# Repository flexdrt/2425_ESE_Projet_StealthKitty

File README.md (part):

# 🐱 **StealthKitty - Projet Robot Chat**  

---

## 📜 **Description**  
StealthKitty est un projet de **système embarqué innovant** basé sur un **STM32**.  
🎯 **Objectif :** Développer plusieurs robots capables de se déplacer sur une table sans bordure.  

- 🐾 Un robot est désigné comme chat et doit attraper un autre robot, qui devient alors le nouveau chat.  

Ce projet est réalisé dans le cadre de la dernière année de la filière **électronique et systèmes embarqués (ESE)** de l'ENSEA.

### **Les contributeurs :**  
- 👨‍💻 **Vincent LAKHMECHE**  
- 👨‍💻 **Mohamed Rafik CHAIR**  
- 👨‍💻 **Meziane Ameur**  
- 👨‍💻 **Karim JERJOUB**

---

## 📚 **Table des matières**
1. [📖 Contexte](#-contexte)
2. [📐 Architecture](#-architecture)  
3. [✨ Fonctionnalités](#-fonctionnalités)
4. [📚 Explication Technique](#-Explication-Technique). 
5. [🔧 Matériel utilisé](#-matériel-utilisé)  
6. [🚀 Utilisation](#-utilisation)  
7. [📄 Licence](#-licence)  

---

## 📖 **Contexte**  
Ce projet s'inscrit dans le cadre de la formation 3A à l'ENSEA.  
🎯 L'objectif est de concevoir un système embarqué complet, depuis la conception électronique jusqu'à l'implémentation logicielle.

---

## 📐 **Architecture**  
### **Schéma architectural**  

Ce schéma ne détaille pas que chaque moteur a sa propre pwm et son driver propre également.

## Explication du fonctionnement du système

1. **⚡ Alimentation principale**
   - La **batterie NiMH 7.2V 1.3Ah** alimente l'ensemble du système. Elle est connectée à des régulateurs de tension pour fournir les différentes tensions nécessaires aux composants :
     - **MP1475S** : Régulateur 5V pour alimenter les moteurs et certains capteurs.
     - **BU33SD5WG-TR** : Régulateur 3.3V pour alimenter le microcontrôleur STM32G431, l'accéléromètre et le LiDAR.

2. **🖥️ Microcontrôleur principal - STM32G431**
   - Le **STM32G431** gère toute la logique du robot et communique avec les différents composants via des bus tels que SPI, UART, I2C.
   - Il est relié à un **quartz 16 MHz** pour la gestion de l'horloge système et dispose d'un connecteur **SWD** pour la programmation et le débogage.

3. **🔍 Capteurs**
   - **Capteurs ToF** : Utilisés pour détecter les bords ou les chutes du robot.
   - **ADXL343 (Accéléromètre)** : Détecte les impacts ou les tapotements, utilisé pour détecter les collisions avec d'autres robots, et connecté au bus **SPI**.
   - **LiDAR YDLIDAR X4** : Permet de détecter les obstacles à l'aide de la communication **UART** pour transmettre les données de distance et d'angle.

4. **⚙️ Contrôle des moteurs**
   - **ZXBM5210-SP-13 (Driver de moteur)** : Utilisé pour contrôler la direction et la vitesse des moteurs à l'aide de signaux **PWM**. Le microcontrôleur STM32 contrôle les moteurs via le driver pour ajuster la vitesse et la direction du robot.

5. **🌟 Indicateurs d'état (LEDs)**
   - Les **LEDs** servent d'indicateurs pour visualiser l'état du robot, par exemple, lorsqu'il est en marche ou lorsqu'il détecte un obstacle.

### Détails des principaux outils utilisés

1. **Communication avec l'accéléromètre (ADXL343)**
   - Utilisation du protocole **SPI** pour lire les données des axes X, Y et Z.
   - Détection des chocs (taps) causés par des collisions avec d'autres robots.

2. **Contrôle des moteurs avec le driver ZXBM5210**
   - Génération de signaux **PWM** pour réguler la vitesse des moteurs.
   - Implémentation des mouvements du robot : avancer, reculer, tourner à gauche ou à droite.

3. **Gestion des capteurs de bordure/détection de chute**
   - Lecture des entrées des capteurs pour détecter les bords de la table.
   - Réaction immédiate pour stopper ou changer de direction afin d’éviter une chute.

4. **Interfaçage avec le LiDAR YDLIDAR X4**
   - Communication via **UART** pour lire les données du LiDAR ainsi détecter les autres robots.
   - Extraction des valeurs d’angles et de distances pour cartographier l'environnement et éviter les obstacles.

---

## ✨ **Fonctionnalités**  
- 🛡️ **Détection de bords** via des capteurs ToF.  
- 🔄 **Communication entre robots** pour synchronisation.  
- 🎯 **Algorithme de poursuite et d'évitement.**  
- ⚙️ **Gestion des moteurs**
  
## 📚 Explication Technique

#  ⚡Accéléromètre ADXL343 dans le robot chat

<details>
<summary> Détail  sur l'utilisation de l'accéléromètre ADXL343 </summary>

## 🎯 Objectifs principaux
- ✨ **Détecter les tapotements** (Single Tap/Double Tap) pour **changer de rôle** entre le robot dans l'état "chat" et dans l'état "souris".
- 📊 Lire les valeurs d'accélération sur les axes **X, Y, Z** *(optionnel)*.

---

## ⚙️ Configuration
- **Plage d'accélération :** ±2 g *(précision pour petits mouvements)*.
- **Registres utilisés :**  
  - 🛠️ `POWER_CTL` : Activer le mode mesure.  
  - 🎚️ `THRESH_TAP`, `DUR`, `INT_ENABLE` : Configurer les seuils et activer les interruptions pour les tapotements.  
  - 🖥️ `INT_SOURCE` : Vérifier les événements de tapotements.

---

## 🔧 Fonctionnalités implémentées
### ✅ Détection des tapotements
- 🔄 Vérifie les interruptions via le registre `INT_SOURCE`.
- 📍 Met à jour la variable globale `tap_detected` pour signaler un événement.

### ✅ Lecture des accélérations
- 📥 Récupération des valeurs brutes : `acc_rawX`, `acc_rawY`, `acc_rawZ`.
- 🔄 Conversion des valeurs en unités normalisées (*g*) via un facteur de calibration.

---

## 🔁 Réactions aux tapotements
- ⚡ **Interruptions activées** pour permettre une réaction en temps réel.
- 🔀 Chaque tapotement entraîne un **changement de comportement des moteurs** (ex. direction ou rôle).

---

## 🕒 FreeRTOS Task
- Création d'une tâche principale **`vTaskADX`** pour :  
  1️⃣ Lire les données d'accélération brutes et normalisées.  
  2️⃣ Vérifier les événements de tapotement.  
  3️⃣ Ajouter un délai pour réduire la charge CPU (`vTaskDelay`).

---

https://github.com/user-attachments/assets/b687c830-fabb-43c3-ac29-a924f9b9cf93

</details>

# 📡Capteur ToF VL53L1X pour détection des bords
<details>
<summary> Détail sur l'utilisation du capteur ToF VL53L1X pour la détection des bords </summary>

## 🌟 Caractéristiques techniques

- 📡 **Technologie :** ToF (Time of Flight)
- 🕐 **Plage de mesure :** 4 mm à 4 m (en mode longue distance)
- ⏳ **Budget temporel :** Configurable entre 15 ms et 500 ms
  - 15 ms : mode court pour une réactivité accrue
  - 500 ms : mode long pour une meilleure précision
- 🔄 **Mode de distance :**
  - Court (1,3 m max) : meilleure immunité au bruit ambiant
  - Long (4 m max) : portée étendue pour des environnements sombres
- 🌌 **Précision :** ±1% dans des conditions optimales (100 mm cible, reflectance 17%)
- 🔐 **Interface :** I²C (adresse par défaut : 0x52)
- 🕒 **Temps d'inter-mesure :** Configurable selon le budget temporel

---

## ⚙️ Initialisation et communication

### Interface

- Communication via le port **hi2c1**.
- Configuration par défaut :
  - Mode de distance : Long (`VL53L1__DISTANCE_MODE = 2`)
  - Budget temporel : 20 ms (`VL53L1__TIMING_BUDGET = 20`)
  - Période d'inter-mesure : 25 ms (budget + delta)

### Fonction d'initialisation

```c
uint8_t VL53L1__Init() {
    uint8_t status = 0;
    printf("Initialisation du capteur VL53L1X...\n");
    status |= VL53L1X_SensorInit(TOF_ADDR);
    if (status != 0) {
        printf("Erreur lors de l'initialisation du capteur !\n");
        return status;
    }
    status |= VL53L1X_SetDistanceMode(TOF_ADDR, VL53L1__DISTANCE_MODE);
    status |= VL53L1X_SetTimingBudgetInMs(TOF_ADDR, VL53L1__TIMING_BUDGET);
    status |= VL53L1X_SetInterMeasurementInMs(TOF_ADDR, VL53L1__INTERMEASUREMENT);
    printf("Capteur initialisé avec succès.\n");
    return status;
}
```

---

## 🔧 Traitement des données

1. **Acquisition des données :**
   - Utilisation de `VL53L1X_CheckForDataReady()` pour vérifier la disponibilité.
   - Récupération des distances avec `VL53L1X_GetDistance()`.
   - Mesure complétée en fonction du timing budget configuré.

2. **Filtrage et validation :**
   - Contrôle de `RangeStatus` pour éliminer les mesures aberrantes.
   - Comparaison avec des seuils définis pour rejeter les valeurs hors plage.

3. **Analyse :**
   - Calcul des distances moyennes et écart-type pour optimiser la précision.
   - Intégration avec les données des autres capteurs pour la prise de décision globale.

---

## 📊 Analyse et décisions

### Détection d'obstacles

- Un seuil critique est défini (é.g., 250 mm).
- Si la distance mesurée dépasse ce seuil, une action est entreprise pour éviter la collision et la chute avec le bord.
- Exemple de logique d'évitement : ralentir ou pivoter.

### Exemple : Pivot automatique

```c
if (distance > 250) {
    printf("Obstacle détecté : pivot en cours...\n");
    reverse_motors();  // Fonction pour inverser les moteurs
    vTaskDelay(pdMS_TO_TICKS(500)); // Pause pour effectuer le pivot
    forward_motors(); // Reprise de la trajectoire
}
```

---

## 💾 Structure de données

### Paramètres de configuration

```c
#define VL53L1__TIMING_BUDGET 20
#define VL53L1__DISTANCE_MODE 2
#define VL53L1__LOWER_THRESHOLD 0
#define VL53L1__UPPER_THRESHOLD 4000
```

### Stockage des résultats

```c
typedef struct {
    uint8_t Status;       // Statut de la mesure (erreurs incluses)
    uint16_t Distance;    // Distance mesurée en mm
    uint16_t SignalRate;  // Taux de signal en kcps
    uint16_t AmbientRate; // Taux de bruit ambiant
    uint16_t SpadNum;     // Nombre de SPADs actifs
} VL53L1X_Result_t;
```

---

## ↻ Cycle de fonctionnement

1. Initialisation du capteur ToF avec les paramètres prédéfinis.
2. Boucle d'acquisition des distances :
   - Vérification de l'état du capteur.
   - Lecture et validation des données mesurées.
   - Mise à jour des structures de données.
3. Filtrage des mesures aberrantes et analyse des distances.
4. Détection des obstacles et application des consignes aux moteurs.

---

## 🚀 FreeRTOS : Gestion du capteur ToF

### Exemple de tâche FreeRTOS

```c
void vTaskToF(void *argument) {
    uint16_t distance;
    uint8_t range_status;

    for (;;) {
        // Vérification de la disponibilité des données
        VL53L1X_CheckForDataReady(TOF_ADDR, &range_status);
        if (range_status == 0) {
            // Lecture de la distance
            VL53L1X_GetDistance(TOF_ADDR, &distance);
            printf("Distance mesurée : %d mm\n", distance);

            // Détection d'obstacle
            if (distance > 250) {
                printf("Obstacle détecté, exécution d'un pivot.\n");
                reverse_motors();
                vTaskDelay(pdMS_TO_TICKS(500));
                forward_motors();
            }
        }
        // Pause entre les mesures
        vTaskDelay(pdMS_TO_TICKS(100));
    }
}
```

### Gestion des ressources
- Synchronisation avec des **sémaphores** pour la gestion des interruptions.
- Utilisation de **timers FreeRTOS** pour des mesures périodiques précises.

### Points clés
- Priorité des tâches : la tâche de mesure ToF doit avoir une priorité suffisante pour garantir des mises à jour régulières.
- Gestion des erreurs : surveiller les `RangeStatus` pour éviter des comportements inattendus.

---

## 🛠️ Fonctions clés du driver

- `VL53L1X_SensorInit()` : Initialise le capteur avec les valeurs par défaut.
- `VL53L1X_GetDistance()` : Récupère la distance mesurée (mm).
- `VL53L1X_SetTimingBudgetInMs()` : Configure le budget temporel des mesures.
- `VL53L1X_ClearInterrupt()` : Réinitialise les interruptions après une mesure.
- `VL53L1X_SetDistanceMode()` : Change le mode de mesure (écourté ou étendu).

---

## ⚠️ Points critiques

- Gestion des interruptions I²C et des erreurs de communication.
  - Implémentation robuste pour minimiser les échecs de transfert.
- Calibration régulière pour minimiser les erreurs systématiques.
  - Offset et cross-talk à recalibrer selon l'environnement.
- Ajustement des seuils selon les conditions environnementales :
  - Température ambiante et réflectance des surfaces peuvent affecter les mesures.

https://github.com/user-attachments/assets/b8a1714b-683e-4680-be36-7b728edb92a1

</details>

# 🛠️Contrôle des Moteurs et Encodeurs

<details>
<summary> Détail sur le contrôle des Moteurs et sur les Encodeurs </summary>

## 🛠️ Composants utilisés

Les moteurs utilisés sont des motoréducteurs de la marque DFRobot, les modèles FIT 052X équipés d'un encodeur à quadrature.

Nos moteurs ont une vitesse différentes pour un même rapport cyclique, cependant la différence de vitesse varie en fonction des rapports cycliques choisis, nous n'avons pas pu compenser cette erreur de manière durable et fiable. 
Cela a aussi rendu plus complexe l'implémentation des asservisssements en vitesse et en angle qui devaient prendre en compte ce problème.

## 🚗 Moteurs

Le contrôle des moteurs est effectué à l'aide d'un driver. Ce driver contient plusieurs fonctions pour contrôler la direction et la vitesse des moteurs du robot.

### Fonctionnalités du driver :

- **`void init_motors(void);`** : Initialisation des moteurs.
- **`void forward_r(uint16_t alpha);`** : Faire avancer le moteur droit.
- **`void forward_l(uint16_t alpha);`** : Faire avancer le moteur gauche.
- **`void reverse_r(uint16_t alpha);`** : Faire reculer le moteur droit.
- **`void reverse_l(uint16_t alpha);`** : Faire reculer le moteur gauche.
- **`void stop_r(void);`** : Arrêter le moteur droit.
- **`void stop_l(void);`** : Arrêter le moteur gauche.

### 🔧 Considérations mécaniques

Le robot utilise deux moteurs, un pour chaque roue :

- La roue droite est en **rouge** et la roue gauche est en **bleue**.
- Les roues tournent dans des directions opposées pour permettre au robot de se déplacer en avant ou en arrière.

### 🔄 Sens de marche

| Moteur Gauche  | Sens de marche Robot | Moteur Droit |
| -------------- | -------------------- | ------------ |
| Sens **reverse** | Sens **forward** | Sens **forward** |

Pour avoir le sens de marche du robot en arrière, le tableau est le même sauf que l'on change le sens de chaque moteur.

---

## 🚀 Fonctionnement des moteurs

### Mise en mouvement
- **Avancer** :
  - `forward_r(uint16_t alpha)` : Configure le moteur droit pour avancer en réglant le rapport cyclique PWM sur la valeur spécifiée par `alpha`. Cela contrôle la vitesse de rotation du moteur droit. **Point critique** : Assurez-vous que `alpha` reste dans les limites de la plage autorisée pour éviter de surcharger le moteur.
  - `forward_l(uint16_t alpha)` : Configure le moteur gauche pour avancer avec un fonctionnement similaire au moteur droit.

- **Reculer** :
  - `reverse_r(uint16_t alpha)` : Inverse la polarité pour le moteur droit afin qu'il recule. Le rapport cyclique PWM `alpha` détermine la vitesse en mode reverse. **Point critique** : La synchronisation entre les moteurs est essentielle pour un déplacement précis.
  - `reverse_l(uint16_t alpha)` : Applique le même principe pour le moteur gauche.

### Arrêt
- `stop_r()` : Arrête le moteur droit en mettant le signal PWM à zéro et en désactivant le canal PWM correspondant. **Point critique** : Un arrêt brusque peut endommager le système mécanique si des forces importantes sont en jeu.
- `stop_l()` : Arrête le moteur gauche de manière similaire pour immobiliser le robot.

---

## 🔧 Encodeurs
Les encodeurs mesurent la rotation des moteurs pour calculer leur position et leur vitesse. Ces données sont essentielles pour un contrôle précis. Un test en vidéo des encodeurs est visible plus haut dans ce document, dans la partie "Détail sur l'utilisation de l'accéléromètre ADXL343" (on peut voir la vitesse du moteur droit et gauche). 

### Fonctions principales
1. **Position** :
   - `get_encoder_position(uint8_t motor)` : Retourne la position actuelle en impulsions pour le moteur spécifié (gauche ou droit). Cette valeur est obtenue en lisant le compteur du timer associé à l'encodeur. **Point critique** : Une dérive dans les valeurs peut indiquer un problème de calibration ou de bruit.

2. **Réinitialisation** :
   - `reset_encoder(uint8_t motor)` : Réinitialise la valeur du compteur de l'encodeur à zéro, permettant de redémarrer les mesures à partir d'une référence claire. **Point critique** : Réinitialisez uniquement lorsque les moteurs sont à l'arrêt pour éviter des erreurs de mesure.

3. **Vitesse** :
   - `calculate_motor_speed(uint8_t motor, uint32_t delta_time_ms, uint16_t encoder_resolution)` : Calcule la vitesse en tours par seconde à partir des différences de positions mesurées par l'encodeur sur une durée spécifiée. La résolution de l'encodeur (en impulsions par tour) est utilisée pour la conversion. **Point critique** : Le choix d'un intervalle de temps trop court peut amplifier le bruit dans les calculs de vitesse.

---

## 🛠 Contrôle PID
Le contrôle PID ajuste dynamiquement la commande des moteurs pour maintenir une vitesse cible.

- `compute_pid(float target_speed, float measured_speed, float *integral_error, float *previous_error, float kp, float ki, float kd)` :
  - **Entrées** :
    - `target_speed` : La vitesse souhaitée pour le moteur.
    - `measured_speed` : La vitesse réelle mesurée par l'encodeur.
    - `integral_error` : Accumulation des erreurs précédentes pour l'effet intégral.
    - `previous_error` : Dernière erreur enregistrée pour l'effet dérivé.
    - `kp`, `ki`, `kd` : Gains proportionnel, intégral et dérivé.
  - **Sortie** :
    - Une commande ajustée à appliquer au moteur pour corriger l'écart entre la vitesse cible et mesurée. **Point critique** : Un mauvais réglage des gains PID peut entraîner des oscillations ou une réponse lente.

---

## 🛠 Modes de fonctionnement

### Mode "Souris"
- **Objectif** : Déplacement à vitesse modérée.
- Les fonctions `forward_r()` et `forward_l()` configurent les moteurs pour avancer avec un rapport cyclique moyen (environ 40%).
- La vitesse et la position de chaque moteur sont mesurées et affichées périodiquement.
- Ce mode est conçu pour une navigation fluide et contrôlée. **Point critique** : Surveiller les variations de vitesse pour éviter les dérapages.

### Mode "Prédateur"
- **Objectif** : Déplacement rapide pour des actions dynamiques.
- Les moteurs fonctionnent à un rapport cyclique plus élevé (environ 70-80%).
- Ce mode est idéal pour des courses ou des approches agressives nécessitant une réponse rapide. **Point critique** : Les moteurs peuvent surchauffer si le mode est utilisé trop longtemps sans pauses.

### Pivot Arrière
- **Objectif** : Éviter les obstacles en pivotant.
- Les moteurs sont commandés pour reculer à des vitesses différentes, créant une rotation du robot.
- Exemple : Le moteur droit recule rapidement tandis que le gauche recule lentement, produisant une rotation autour d'un axe.
- Après le pivot, les moteurs reprennent leur fonctionnement normal. **Point critique** : Assurez-vous que le sol offre suffisamment d'adhérence pour un pivot efficace.

---

## 💡 Notes Techniques
- **Timers** :
  - TIM1 : Gère les signaux PWM pour le contrôle des moteurs.
  - TIM3 : Utilisé pour l'encodeur du moteur droit.
  - TIM4 : Utilisé pour l'encodeur du moteur gauche.

- **Résolution** :
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
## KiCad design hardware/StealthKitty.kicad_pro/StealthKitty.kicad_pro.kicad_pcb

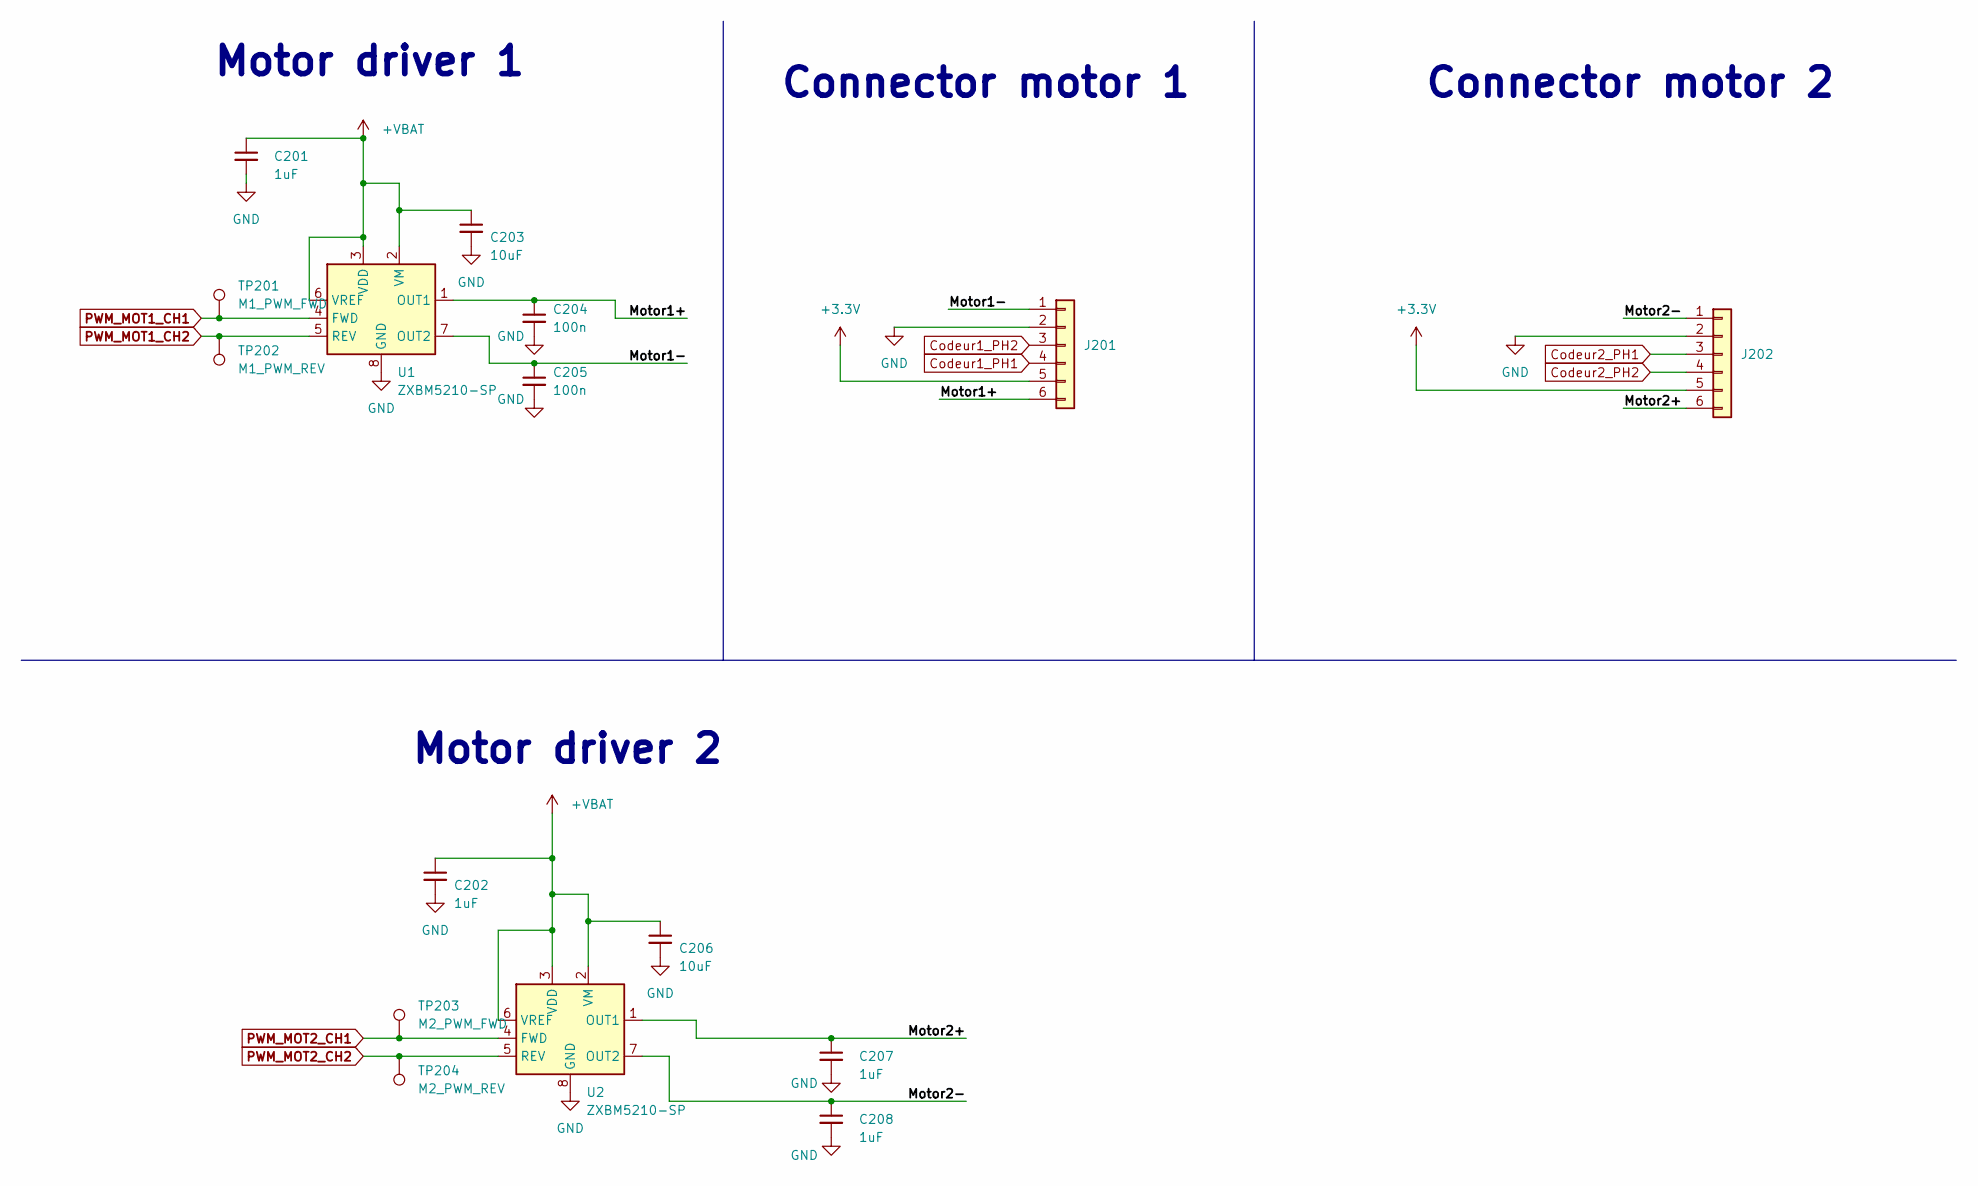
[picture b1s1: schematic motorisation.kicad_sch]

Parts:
C201, C202, C207, C208: 1uF; C_0603_1608Metric
C203, C206: 10uF; C_0603_1608Metric
C204, C205: 100n; C_0402_1005Metric
J201, J202: Conn_01x06; JST_XH_S6B-XH-A_1x06_P2.50mm_Horizontal
TP201: M1_PWM_FWD; TestPoint_Pad_D1.5mm
TP202: M1_PWM_REV; TestPoint_Pad_D1.5mm
TP203: M2_PWM_FWD; TestPoint_Pad_D1.5mm
TP204: M2_PWM_REV; TestPoint_Pad_D1.5mm
U1, U2: ZXBM5210-SP; Diodes_SO-8EP

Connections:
+3.3V: J201.5, J202.5; also elsewhere on the board
+VBAT: C201.1, C202.1, C203.1, C206.1, U1.2 (VM), U1.3 (VDD), U1.6 (VREF), U2.2 (VM), U2.3 (VDD), U2.6 (VREF); also elsewhere on the board
/Motorisation Sheet/Motor1+: C204.1, J201.6, U1.1 (OUT1)
/Motorisation Sheet/Motor1-: C205.1, J201.1, U1.7 (OUT2)
/Motorisation Sheet/Motor2+: C207.1, J202.6, U2.1 (OUT1)
/Motorisation Sheet/Motor2-: C208.1, J202.1, U2.7 (OUT2)
Codeur1_PH1: J201.4; also elsewhere on the board
Codeur1_PH2: J201.3; also elsewhere on the board
Codeur2_PH1: J202.3; also elsewhere on the board
Codeur2_PH2: J202.4; also elsewhere on the board
GND: C201.2, C202.2, C203.2, C204.2, C205.2, C206.2, C207.2, C208.2, J201.2, J202.2, U1.8 (GND), U1.9 (GND), U2.8 (GND), U2.9 (GND); also elsewhere on the board
PWM_MOT1_CH1: TP201.1, U1.4 (FWD); also elsewhere on the board
PWM_MOT1_CH2: TP202.1, U1.5 (REV); also elsewhere on the board
PWM_MOT2_CH1: TP203.1, U2.4 (FWD); also elsewhere on the board
PWM_MOT2_CH2: TP204.1, U2.5 (REV); also elsewhere on the board

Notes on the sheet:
Motor driver 1
Connector motor 2
Connector motor 1
Motor driver 2

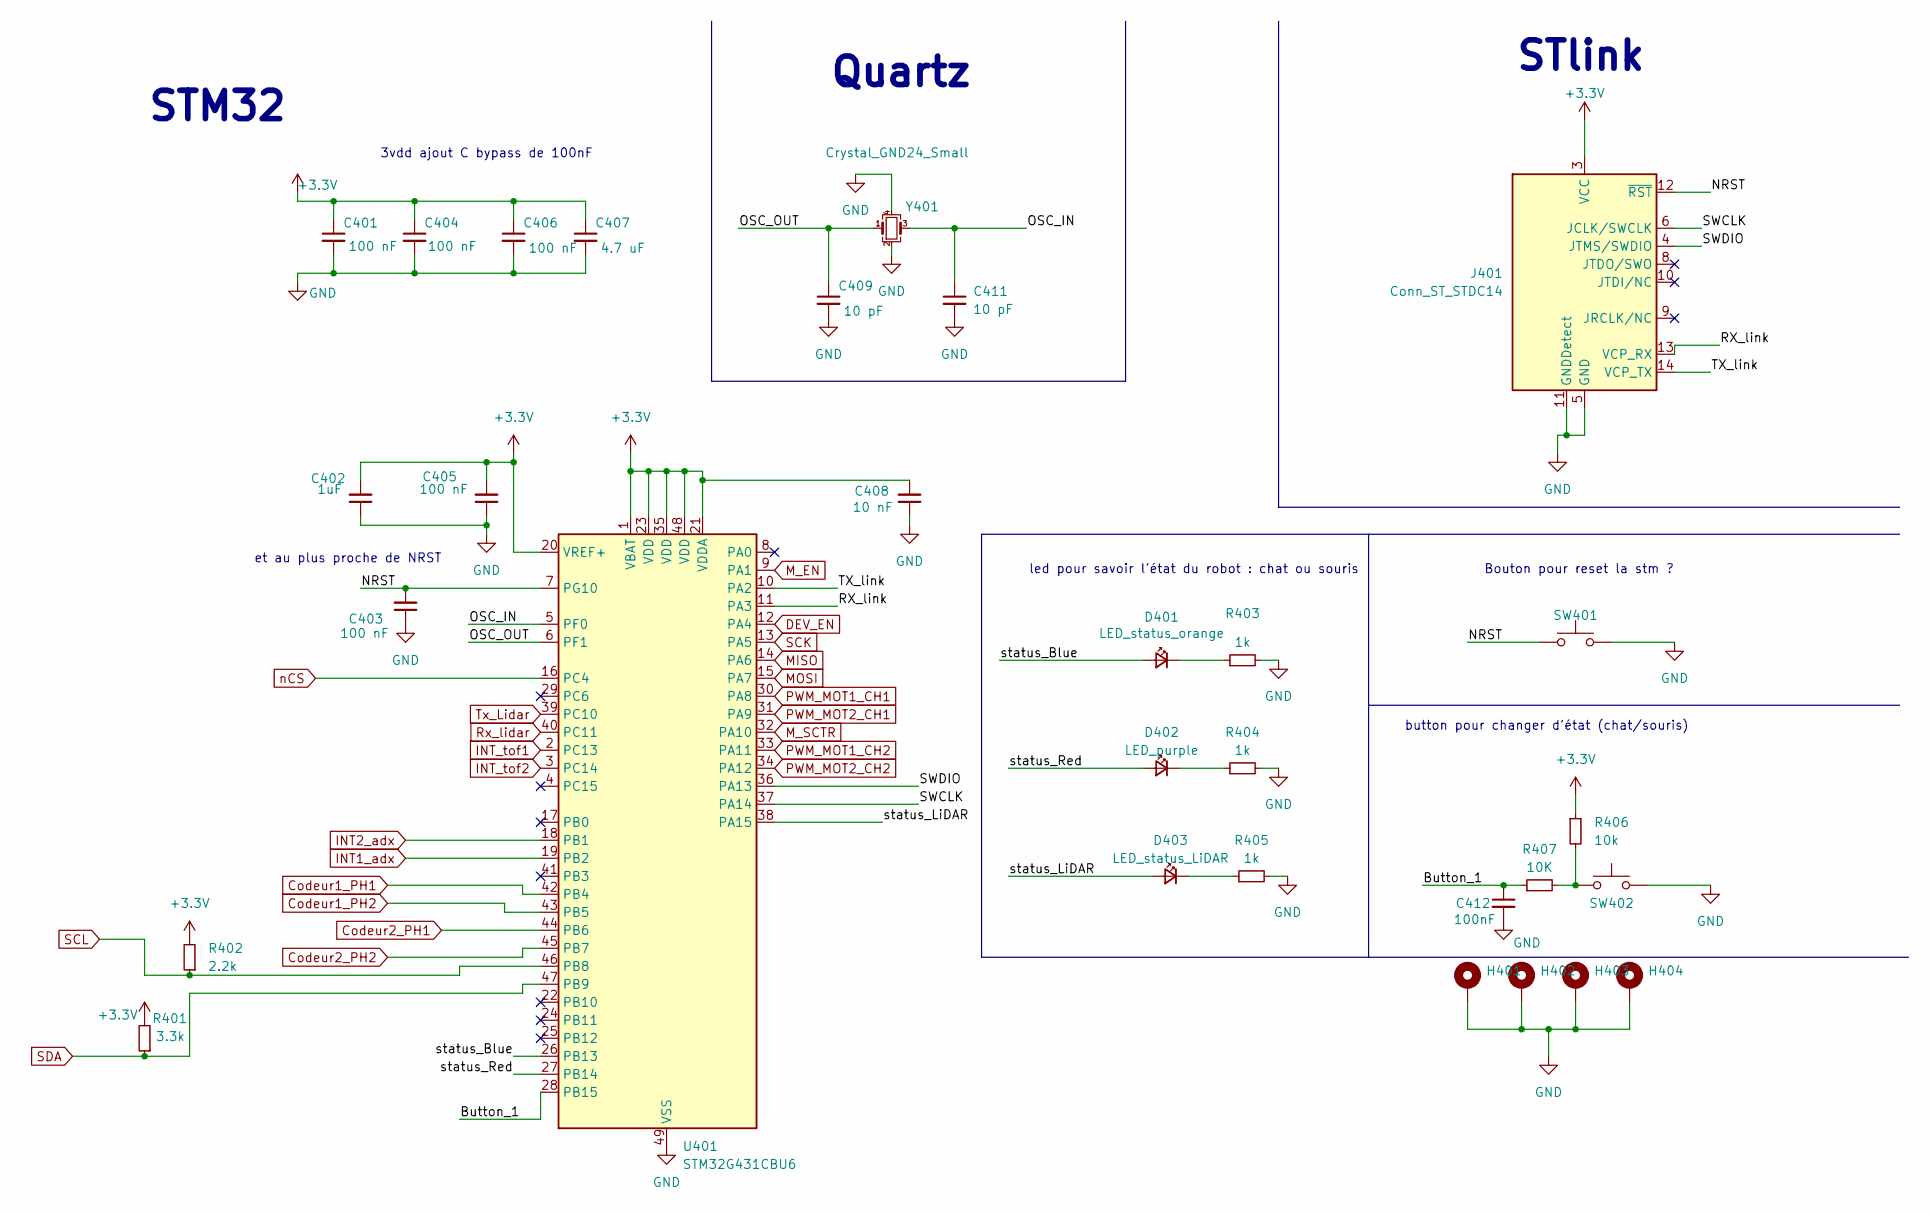
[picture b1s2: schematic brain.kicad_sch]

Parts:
C401, C403, C404, C405, C406: 100 nF; C_0402_1005Metric
C402: 1uF; C_0603_1608Metric
C407: 4.7 uF; C_0603_1608Metric
C408: 10 nF; C_0402_1005Metric
C409, C411: 10 pF; C_0402_1005Metric
C412: 100nF; C_0402_1005Metric
D401: LED_status_orange; LED_0603_1608Metric_Pad1.05x0.95mm_HandSolder
D402: LED_purple; LED_0603_1608Metric_Pad1.05x0.95mm_HandSolder
D403: LED_status_LiDAR; LED_0603_1608Metric_Pad1.05x0.95mm_HandSolder
H401, H402, H403, H404: MountingHole_3.2mm_M3_Pad_Via
J401: Conn_ST_STDC14; PinHeader_2x07_P1.27mm_Vertical_SMD
R401: 3.3k; R_0402_1005Metric
R402: 2.2k; R_0402_1005Metric
R403, R404, R405: 1k; R_0402_1005Metric
R406: 10k; R_0402_1005Metric
R407: 10K; R_0402_1005Metric
SW401, SW402: SW_Push; SW_Push_1P1T_NO_6x6mm_H9.5mm
U401: STM32G431CBU6; QFN-48-1EP_7x7mm_P0.5mm_EP5.6x5.6mm
Y401: Crystal_GND24_Small; Crystal_SMD_3225-4Pin_3.2x2.5mm

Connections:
+3.3V: C401.1, C402.2, C404.1, C405.2, C406.1, C407.1, C408.2, J401.3 (VCC), R401.2, R402.2, R406.1, U401.1 (VBAT), U401.20 (VREF+), U401.21 (VDDA), U401.23 (VDD), U401.35 (VDD), U401.48 (VDD); also elsewhere on the board
/Brain Sheet/Button_1: C412.1, R407.1, U401.28 (PB15)
/Brain Sheet/NRST: C403.2, J401.12 (~RST), SW401.1, U401.7 (PG10)
/Brain Sheet/OSC_IN: C411.1, U401.5 (PF0), Y401.3
/Brain Sheet/OSC_OUT: C409.1, U401.6 (PF1), Y401.1
/Brain Sheet/RX_link: J401.13 (VCP_RX), U401.11 (PA3)
/Brain Sheet/SWCLK: J401.6 (JCLK/SWCLK), U401.37 (PA14)
/Brain Sheet/SWDIO: J401.4 (JTMS/SWDIO), U401.36 (PA13)
/Brain Sheet/TX_link: J401.14 (VCP_TX), U401.10 (PA2)
/Brain Sheet/status_Blue: D401.2 (A), U401.26 (PB13)
/Brain Sheet/status_LiDAR: D403.2 (A), U401.38 (PA15)
/Brain Sheet/status_Red: D402.2 (A), U401.27 (PB14)
Codeur1_PH1: U401.42 (PB4); also elsewhere on the board
Codeur1_PH2: U401.43 (PB5); also elsewhere on the board
Codeur2_PH1: U401.44 (PB6); also elsewhere on the board
Codeur2_PH2: U401.45 (PB7); also elsewhere on the board
DEV_EN: U401.12 (PA4); also elsewhere on the board
GND: C401.2, C402.1, C403.1, C404.2, C405.1, C406.2, C407.2, C408.1, C409.2, C411.2, C412.2, H401.1, H402.1, H403.1, H404.1, J401.5 (GND), J401.7 (GND), J401.11 (GNDDetect), R403.2, R404.2, R405.2, SW401.2, SW402.2, U401.49 (VSS), Y401.2, Y401.4; also elsewhere on the board
INT1_adx: U401.19 (PB2); also elsewhere on the board
INT2_adx: U401.18 (PB1); also elsewhere on the board
INT_tof1: U401.2 (PC13); also elsewhere on the board
INT_tof2: U401.3 (PC14); also elsewhere on the board
MISO: U401.14 (PA6); also elsewhere on the board
MOSI: U401.15 (PA7); also elsewhere on the board
M_EN: U401.9 (PA1); also elsewhere on the board
M_SCTR: U401.32 (PA10); also elsewhere on the board
unnamed: D401.1 (K), R403.1
unnamed: D402.1 (K), R404.1
unnamed: D403.1 (K), R405.1
unnamed: R406.2, R407.2, SW402.1
PWM_MOT1_CH1: U401.30 (PA8); also elsewhere on the board
PWM_MOT1_CH2: U401.33 (PA11); also elsewhere on the board
PWM_MOT2_CH1: U401.31 (PA9); also elsewhere on the board
PWM_MOT2_CH2: U401.34 (PA12); also elsewhere on the board
Rx_lidar: U401.40 (PC11); also elsewhere on the board
SCK: U401.13 (PA5); also elsewhere on the board
SCL: R402.1, U401.46 (PB8); also elsewhere on the board
SDA: R401.1, U401.47 (PB9); also elsewhere on the board
Tx_Lidar: U401.39 (PC10); also elsewhere on the board
nCS: U401.16 (PC4); also elsewhere on the board

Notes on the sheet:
Quartz
et au plus proche de NRST
STM32
led pour savoir l'état du robot : chat ou souris
3vdd ajout C bypass de 100nF
Bouton pour reset la stm ?
STlink
button pour changer d'état (chat/souris)

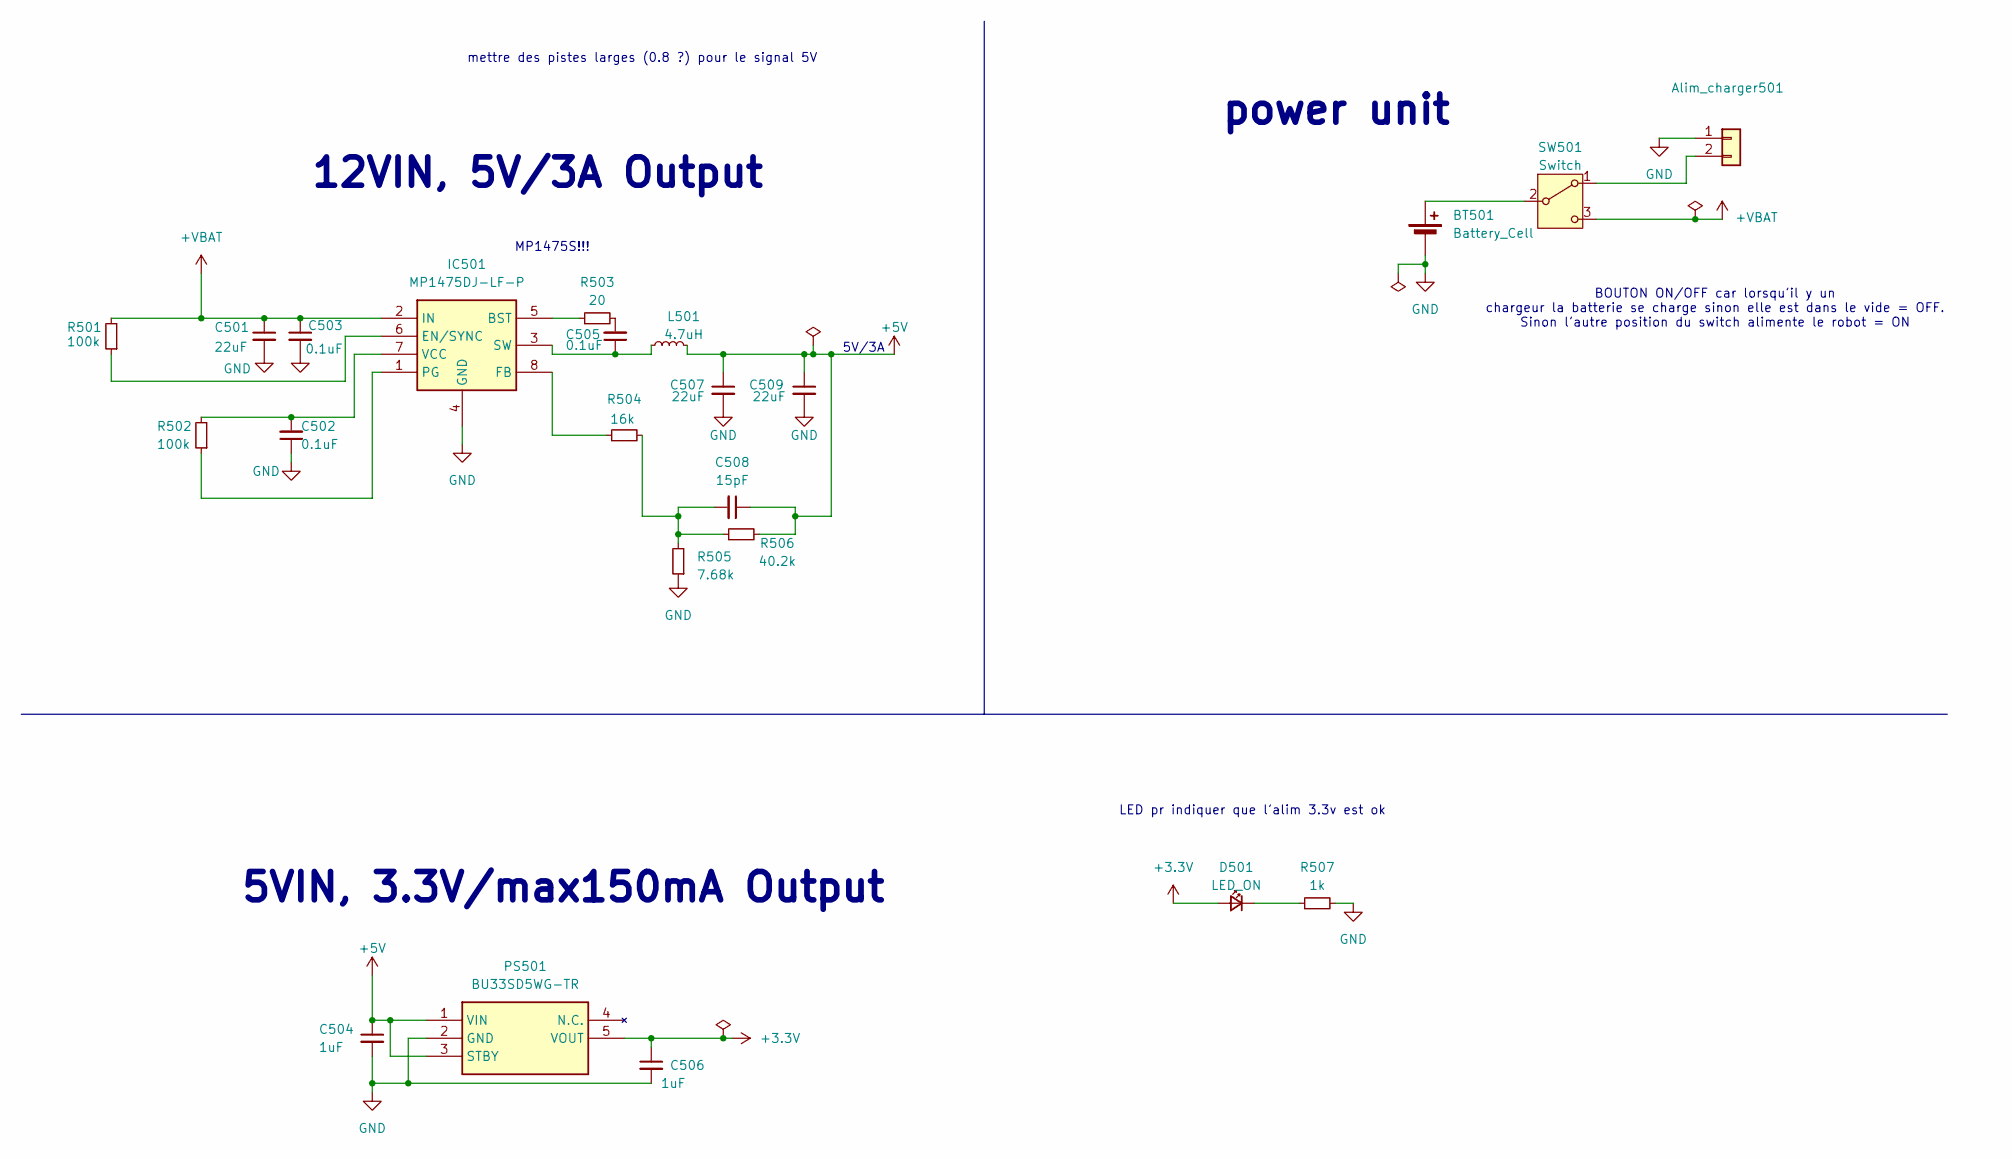
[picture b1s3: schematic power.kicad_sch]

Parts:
Alim_charger501: Conn_01x02; JST_XH_S2B-XH-A-1_1x02_P2.50mm_Horizontal
BT501: Battery_Cell; JST_XH_S2B-XH-A-1_1x02_P2.50mm_Horizontal
C501, C507, C509: 22uF; C_0805_2012Metric
C502, C503, C505: 0.1uF; C_0402_1005Metric
C504, C506: 1uF; C_0603_1608Metric
C508: 15pF; C_0402_1005Metric
D501: LED_ON; LED_0603_1608Metric_Pad1.05x0.95mm_HandSolder
IC501: MP1475DJ-LF-P; SOT65P280X100-8N; Mouser Part Number 946-MP1475DJLFP
L501: 4.7uH; INDPM5050X200N; Manufacturer_Part_Number 74438356047HT; Mouser Part Number 710-74438356047HT
PS501: BU33SD5WG-TR; SOT95P280X125-5N; Manufacturer_Part_Number BU33SD5WG-TR; Mouser Part Number 755-BU33SD5WG-TR
R501, R502: 100k; R_0402_1005Metric
R503: 20; R_0402_1005Metric
R504: 16k; R_0402_1005Metric
R505: 7.68k; R_0402_1005Metric
R506: 40.2k; R_0402_1005Metric
R507: 1k; R_0402_1005Metric
SW501: Switch; JST_XH_S3B-XH-A-1_1x03_P2.50mm_Horizontal; Manufacturer_Part_Number WS-TOTV Ø 6.35mm; Mouser Part Number 1333652

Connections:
+3.3V: C506.1, D501.2 (A), PS501.5 (VOUT); also elsewhere on the board
+5V: C504.1, C507.1, C508.1, C509.1, L501.2, PS501.1 (VIN), PS501.3 (STBY), R506.2; also elsewhere on the board
+VBAT: C501.1, C503.1, IC501.2 (IN), R501.2, SW501.3 (C); also elsewhere on the board
GND: Alim_charger501.1, BT501.2 (-), C501.2, C502.1, C503.2, C504.2, C506.2, C507.2, C509.2, IC501.4 (GND), PS501.2 (GND), R505.1, R507.2; also elsewhere on the board
unnamed: Alim_charger501.2, SW501.1 (A)
unnamed: BT501.1 (+), SW501.2 (B)
unnamed: C505.2, R503.2
unnamed: C508.2, R504.2, R505.2, R506.1
unnamed: D501.1 (K), R507.1
unnamed: IC501.5 (BST), R503.1
unnamed: IC501.6 (EN/SYNC), R501.1
unnamed: IC501.8 (FB), R504.1
unnamed: IC501.1 (PG), R502.1
unnamed: C505.1, IC501.3 (SW), L501.1
unnamed: C502.2, IC501.7 (VCC), R502.2

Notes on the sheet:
mettre des pistes larges (0.8 ?) pour le signal 5V
12VIN, 5V/3A Output
LED pr indiquer que l'alim 3.3v est ok
5VIN, 3.3V/max150mA Output
MP1475S!!!
5V/3A
power unit
BOUTON ON/OFF car lorsqu'il y un chargeur la batterie se charge sinon elle est dans le vide = OFF. Sinon l'autre position du switch alimente le robot = ON

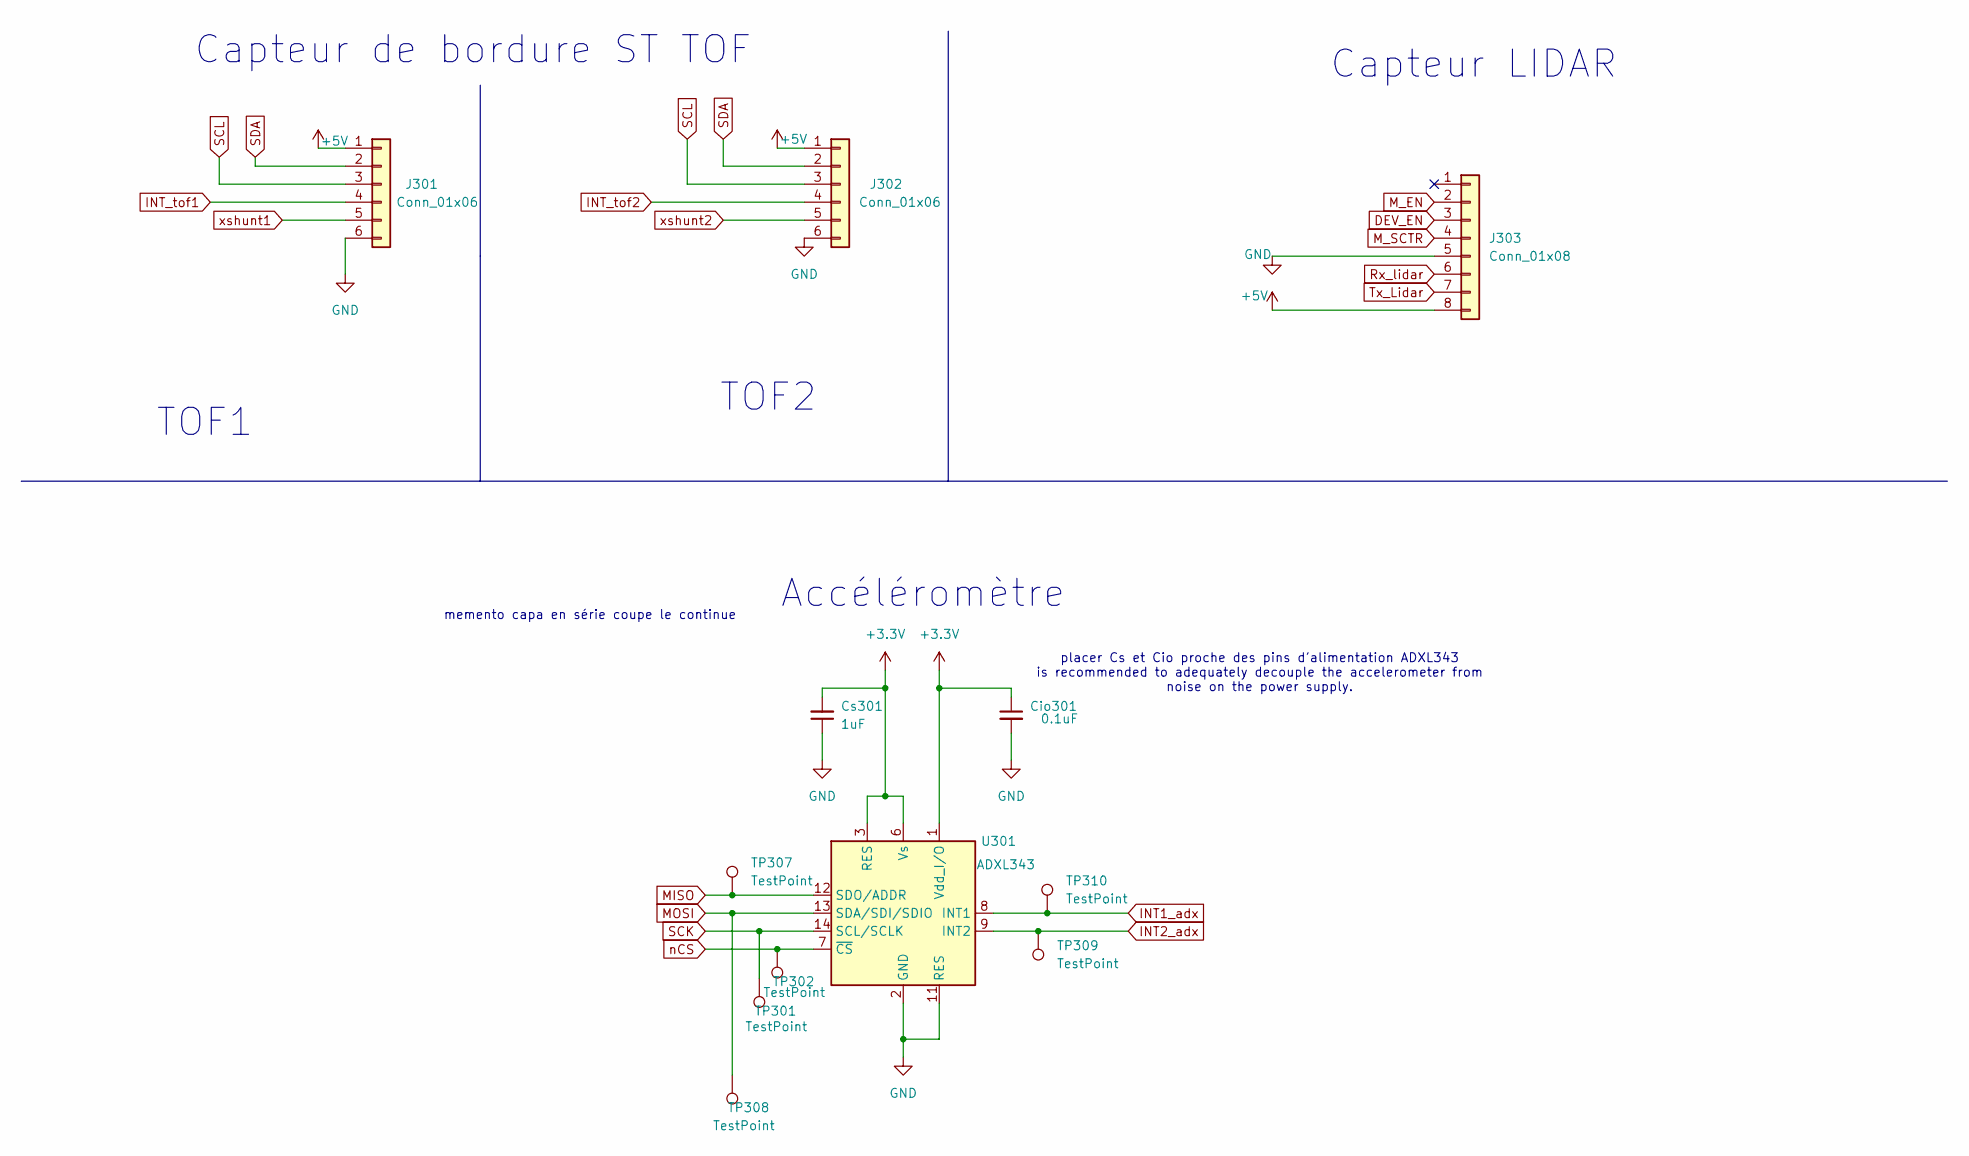
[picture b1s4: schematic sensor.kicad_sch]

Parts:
Cio301: 0.1uF; C_0402_1005Metric
Cs301: 1uF; C_0603_1608Metric
J301, J302: Conn_01x06; JST_XH_S6B-XH-A_1x06_P2.50mm_Horizontal
J303: Conn_01x08; JST_XH_S8B-XH-A_1x08_P2.50mm_Horizontal
TP301, TP302, TP307, TP308, TP309, TP310: TestPoint; TestPoint_Pad_D1.5mm
U301: ADXL343; LGA-14_3x5mm_P0.8mm_LayoutBorder1x6y

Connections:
+3.3V: Cio301.1, Cs301.2, U301.1 (Vdd_I/O), U301.3 (RES), U301.6 (Vs); also elsewhere on the board
+5V: J301.1, J302.1, J303.8; also elsewhere on the board
DEV_EN: J303.3; also elsewhere on the board
GND: Cio301.2, Cs301.1, J301.6, J302.6, J303.5, U301.2 (GND), U301.4 (GND), U301.5 (GND), U301.11 (RES); also elsewhere on the board
INT1_adx: TP310.1, U301.8 (INT1); also elsewhere on the board
INT2_adx: TP309.1, U301.9 (INT2); also elsewhere on the board
INT_tof1: J301.4; also elsewhere on the board
INT_tof2: J302.4; also elsewhere on the board
MISO: TP307.1, U301.12 (SDO/ADDR); also elsewhere on the board
MOSI: TP308.1, U301.13 (SDA/SDI/SDIO); also elsewhere on the board
M_EN: J303.2; also elsewhere on the board
M_SCTR: J303.4; also elsewhere on the board
Rx_lidar: J303.6; also elsewhere on the board
SCK: TP301.1, U301.14 (SCL/SCLK); also elsewhere on the board
SCL: J301.3, J302.3; also elsewhere on the board
SDA: J301.2, J302.2; also elsewhere on the board
Tx_Lidar: J303.7; also elsewhere on the board
nCS: TP302.1, U301.7 (~CS); also elsewhere on the board
xshunt1: J301.5
xshunt2: J302.5

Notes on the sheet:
TOF1
Accéléromètre
memento capa en série coupe le continue
TOF2
Capteur de bordure ST TOF
placer Cs et Cio proche des pins d'alimentation ADXL343 is recommended to adequately decouple the accelerometer from noise on the power supply.
Capteur LIDAR

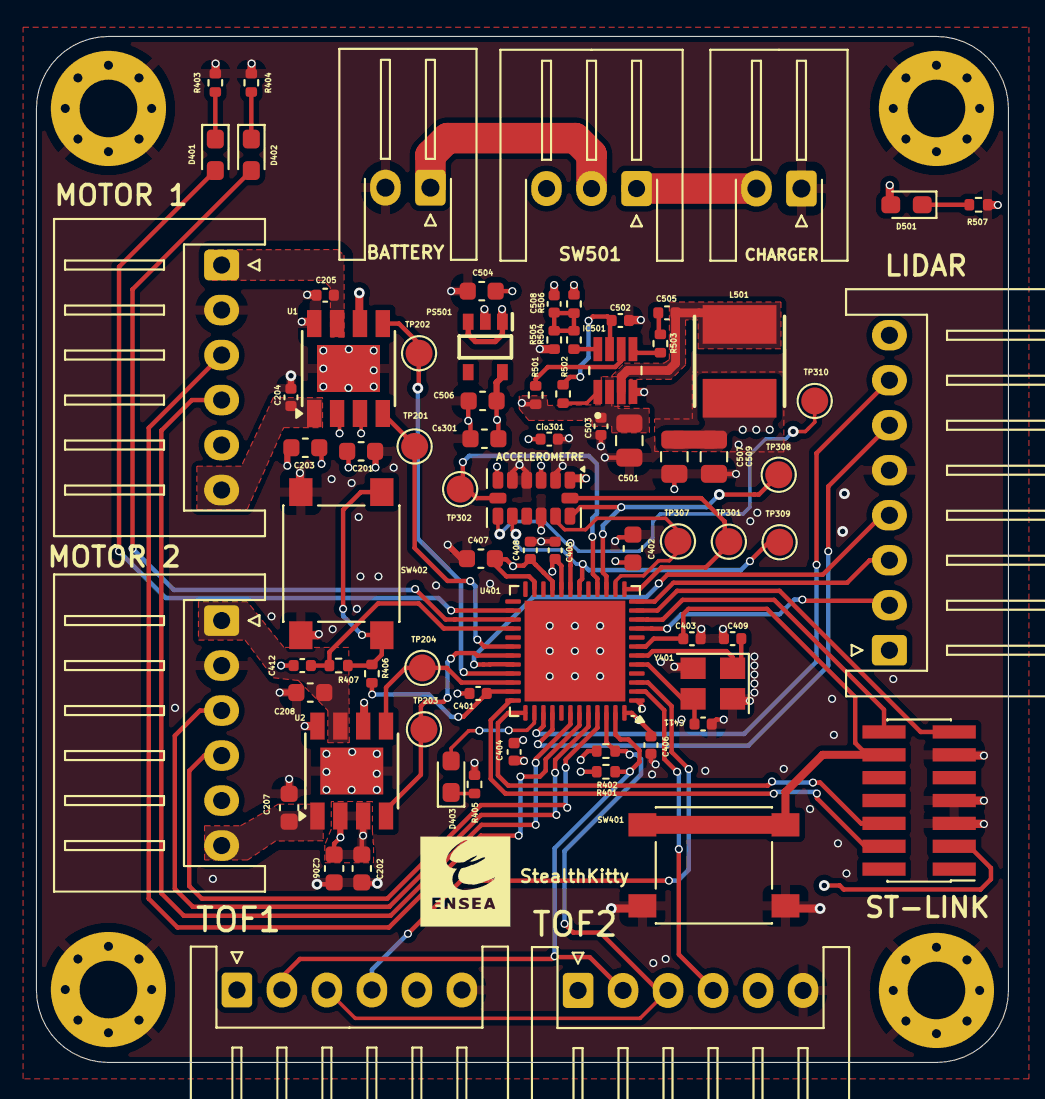
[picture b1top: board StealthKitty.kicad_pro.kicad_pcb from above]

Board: 4 copper layers, 54.0 x 57.0 mm, 81 parts (1 on the bottom side), 57 nets.

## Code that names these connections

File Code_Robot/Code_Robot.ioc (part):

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Mcu.Name=STM32G431C(6-8-B)Ux
Mcu.Package=UFQFPN48
Mcu.UserName=STM32G431CBUx
PA1.GPIOParameters=GPIO_Label
PA1.GPIO_Label=LIDAR M_EN
PA1.Signal=GPIO_Output
PA10.GPIOParameters=GPIO_Label
PA10.GPIO_Label=LIDAR M_SCTR
PA10.Signal=S_TIM1_CH3
PA11.GPIOParameters=GPIO_Label
PA11.GPIO_Label=PWM_MOT1_CH2
PA11.Mode=PWM Generation1 CH1 CH1N
PA11.Signal=TIM1_CH1N
PA12.GPIOParameters=GPIO_Label
PA12.GPIO_Label=PWM_MOT2_CH2
PA12.Mode=PWM Generation2 CH2 CH2N
PA12.Signal=TIM1_CH2N
PA13.Mode=Serial_Wire
PA13.Signal=SYS_JTMS-SWDIO
PA14.Mode=Serial_Wire
PA14.Signal=SYS_JTCK-SWCLK
PA15.GPIOParameters=GPIO_Label
PA15.GPIO_Label=Status_Lidar
PA15.Signal=GPIO_Output
PA2.GPIOParameters=GPIO_Label
PA2.GPIO_Label=TX_link (stlink)
PA2.Mode=Asynchronous
PA2.Signal=USART2_TX
PA3.GPIOParameters=GPIO_Label
PA3.GPIO_Label=RX_link (stlink)
PA3.Mode=Asynchronous
PA3.Signal=USART2_RX
PA4.GPIOParameters=GPIO_Label
PA4.GPIO_Label=LIDAR DEV_EN
PA4.Signal=GPIO_Output
PA5.Mode=Full_Duplex_Master
PA5.Signal=SPI1_SCK
PA6.Mode=Full_Duplex_Master
PA6.Signal=SPI1_MISO
PA7.Mode=Full_Duplex_Master
PA7.Signal=SPI1_MOSI
PA8.GPIOParameters=GPIO_Label
PA8.GPIO_Label=PWM_MOT1_CH1
PA8.Signal=S_TIM1_CH1
PA9.GPIOParameters=GPIO_Label
PA9.GPIO_Label=PWM_MOT2_CH1
PA9.Signal=S_TIM1_CH2
PB1.GPIOParameters=GPIO_Label
PB1.GPIO_Label=INT1_ADX
PB1.Signal=GPXTI1
PB13.GPIOParameters=GPIO_Label
PB13.GPIO_Label=Status_Blue
PB13.Signal=GPIO_Output
PB14.GPIOParameters=GPIO_Label
PB14.GPIO_Label=Status_Red
PB14.Signal=GPIO_Output
PB15.GPIOParameters=GPIO_Label
PB15.GPIO_Label=Bouton_1
PB15.Signal=GPIO_Output
PB2.GPIOParameters=GPIO_Label
PB2.GPIO_Label=INT2_ADX
PB2.Signal=GPXTI2
PB4.GPIOParameters=GPIO_Label
PB4.GPIO_Label=Codeur1_PH1
PB4.Signal=S_TIM3_CH1
PB5.GPIOParameters=GPIO_Label
PB5.GPIO_Label=Codeur1_PH2
PB5.Signal=S_TIM3_CH2
PB6.GPIOParameters=GPIO_Label
PB6.GPIO_Label=Codeur2_PH1
PB6.Signal=S_TIM4_CH1
PB7.GPIOParameters=GPIO_Label
PB7.GPIO_Label=Codeur2_PH2
PB7.Signal=S_TIM4_CH2
PB8-BOOT0.GPIOParameters=GPIO_Label
PB8-BOOT0.GPIO_Label=SCL_TOF
PB8-BOOT0.Mode=I2C
PB8-BOOT0.Signal=I2C1_SCL
PB9.GPIOParameters=GPIO_Label
PB9.GPIO_Label=SDA_TOF
PB9.Mode=I2C
PB9.Signal=I2C1_SDA
PC10.GPIOParameters=GPIO_Label
PC10.GPIO_Label=TX_LIDAR
PC10.Mode=Asynchronous
PC10.Signal=UART4_TX
PC11.GPIOParameters=GPIO_Label
PC11.GPIO_Label=RX_LIDAR
PC11.Mode=Asynchronous
PC11.Signal=UART4_RX
PC13.GPIOParameters=GPIO_Label
PC13.GPIO_Label=INT_TOF1
PC13.Signal=GPXTI13
PC14-OSC32_IN.GPIOParameters=GPIO_Label
PC14-OSC32_IN.GPIO_Label=INT_TOF2
PC14-OSC32_IN.Signal=GPXTI14
PC4.GPIOParameters=PinState,GPIO_Label
PC4.GPIO_Label=SPI1_NSS
PC4.PinState=GPIO_PIN_SET
PC4.Signal=GPIO_Output
PF0-OSC_IN.Mode=HSE-External-Oscillator
PF0-OSC_IN.Signal=RCC_OSC_IN
PF1-OSC_OUT.Mode=HSE-External-Oscillator
PF1-OSC_OUT.Signal=RCC_OSC_OUT
RCC.HSE_VALUE=16000000
RCC.SYSCLKFreq_VALUE=16000000
RCC.SYSCLKSource=RCC_SYSCLKSOURCE_HSE
board=custom

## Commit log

2024-09-25 schématique bien avancé
2024-09-25 16:51 :(
2024-09-30 modification i2c labels+ajout R à dimmensionner
2024-10-01 psuh sur le main après revue prof
2024-10-01 Supprimer le répertoire pcb_chat_wawa et ses fichiers
2024-10-01 Ajout des tâches à se partager
2024-10-01 Ajout des tâches à se partager v2
2024-10-01 Modif karim
2024-10-01 Ajout du projet STM32
2024-10-01 MAJ ioc
2024-10-01 Modifications dans ioc
2024-10-01 Sauvegarde des modifications dans language.settings.xml
2024-10-01 Ajout du dossier Software depuis branche_meziane
2024-10-01 Ajout du dossier Software
2024-10-02 MAJ IOC ajout de nv GPIO
2024-10-03 réassignation pins stm32, ajout des modifs de la partie power, ajout des modfis de la revue de projet 02/10/24, modifs du 3/10/24 voir readme
2024-10-03 suppression sous feuille 6,suppression dossier stealthkitty présent dans /hardware
2024-10-03 test suprression sous feuille 3
2024-10-03 MAJ de la partie hardware
2024-10-06 MAJ empreintes
2024-10-07 MAJ routage equipe
2024-10-07 Confirmation placement equipe
2024-10-07 Mise à jour du fichier README.md
2024-10-08 après première revue fiack placement
2024-10-08 Update README.md
    carnet de bord
2024-10-08 Dernier Modif 08/10/2024
2024-10-09 MAJ ioc après placement pour simplifier routage
2024-10-09 readme avant push des autres
2024-10-09 Modification Placement 09/10/24
2024-10-09 Début routage
2024-10-09 MAJ première version routage
2024-10-09 CRCR
2024-10-09 Ajout de README
2024-10-09 Ajout README.md
2024-10-09 Nothing to Commit
2024-10-09 Modif Routage V2
2024-10-10 Modif Routage V3
2024-10-10 Dernier Modif ROUTAGE 10/10/24
2024-10-15 Amélioration de la partie routage
2024-10-16 BomMaj
2024-10-16 Modif PCB 16/10/2024 V1
2024-10-16 MAJ du Readme après revue routage par le prof
2024-10-16 Modif PCB 16/10/2024 V2
2024-10-17 Modif PCB 17/10/2024 V3
2024-10-17 Routage final pour vérification prof
2024-10-22 MODIF PCB 22/10/2024
2024-10-22 Modif après revue du prof le 22/10
2024-10-23 dernier md
2024-10-23 Ajout fichier GERBER
2024-10-23 Ajout fichier GERBER zip
2024-10-23 Ajout fichier GERBER final
2024-10-23 readme spi adx
2024-10-23 MAJ Dossier CUBEIde
2024-10-23 Dernier Modif 23/10/2024
2024-10-23 Regeneration fichier Gerber après ajustement zone pastemask
2024-12-04 ajout Code Robot
2024-12-16 MAJ Code accelerometre
2025-01-07 démarrage des moteurs avec rapport cyclique de 50% incohérent
2025-01-07 gitignore kikad
2025-01-14 ajout images pour readme
2025-01-14 Rename image-20250113151649896.png to driver-schematics-image-20250113151649896.png
2025-01-14 Rename image-20250114113650516.png to driver motor- image-20250114113650516.png
2025-01-14 Rename image-adx-20250114095447270.png to adx-image--20250114095447270.png
2025-01-14 Rename image-lidar-20250114095520915.png to lidar -image-lidar-20250114095520915.png
2025-01-14 readme
2025-01-14 Rename image-20250113151649896.png to tof-image-20250113151649896.png
2025-01-14 Version finale du code avec documentation complète
2025-01-15 Version finale du code avec documentation complète pour doxygene
2025-01-15 Update Doxygen, CodeFinal
2025-01-15 versionning code
2025-01-15 Vidéos
2025-01-15 OrganisationRepos
2025-01-15 repofirmwarefinal
2025-01-15 Clean main.c
2025-01-15 Documentation
2025-01-15 Update README.md
    corrected
    l.357
2025-01-15 Update README.md
    403
2025-01-15 Update README.md
    487
2025-01-15 Update README.md
    747

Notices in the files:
README.md:
📄 **Licence:
📝 Ce projet est sous licence **MIT**.
Pour plus d’informations, consultez le fichier [LICENSE](./LICENSE).
